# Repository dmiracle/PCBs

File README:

Created this file locally, then got it onto github. 133t

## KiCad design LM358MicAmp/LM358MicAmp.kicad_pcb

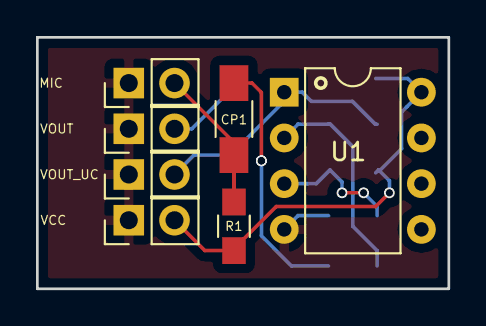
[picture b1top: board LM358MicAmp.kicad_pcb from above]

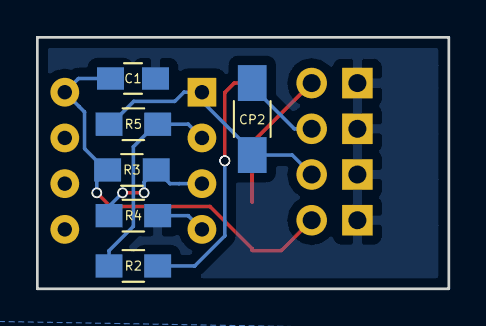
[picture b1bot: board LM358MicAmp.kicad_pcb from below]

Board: 2 copper layers, 22.9 x 14.0 mm, 13 parts (6 on the bottom side), 8 nets.

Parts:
C1: 100nF; C_0805_HandSoldering
CP1: 10uF; C_1206_HandSoldering
CP2: 220uF; C_1206_HandSoldering
MIC: CONN_01X02; Pin_Header_Straight_1x02_Pitch2.54mm
R1, R3, R4: 10K; R_0805_HandSoldering
R2: 1K; R_0805_HandSoldering
R5: 100K; R_0805_HandSoldering
U1: LM358; DIP-8_W7.62mm
VCC: CONN_01X02; Pin_Header_Straight_1x02_Pitch2.54mm
VOUT: CONN_01X02; Pin_Header_Straight_1x02_Pitch2.54mm
VOUT_UC: CONN_01X02; Pin_Header_Straight_1x02_Pitch2.54mm

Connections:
GND: C1.2, MIC.1, R4.2, U1.4, VCC.1, VOUT.1, VOUT_UC.1
MIC: CP1.1, MIC.2, R1.2
unnamed: CP1.2, R2.2
unnamed: R2.1, R5.2, U1.2
unnamed: R3.2, R4.1, U1.3
VCC: C1.1, R1.1, R3.1, U1.8, VCC.2
VOUT: CP2.2, VOUT.2
VOUT_UC: CP2.1, R5.1, U1.1, VOUT_UC.2

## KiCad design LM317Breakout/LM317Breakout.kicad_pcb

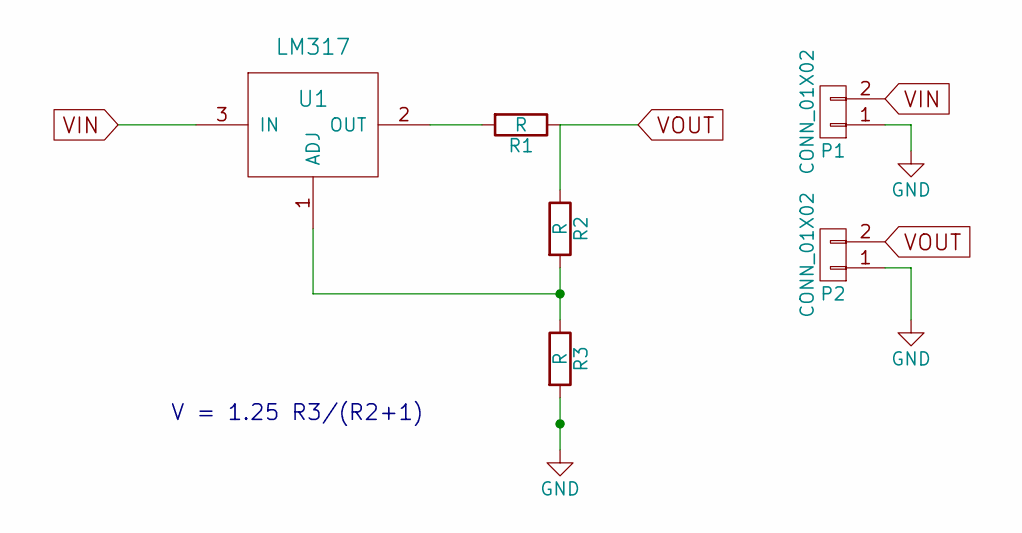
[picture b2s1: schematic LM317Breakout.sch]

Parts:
P1, P2: CONN_01X02; Pin_Header_Straight_1x02_Pitch2.54mm
R1, R2, R3: R; Socket_Strip_Straight_2x01_Pitch2.54mm
U1: LM317; Socket_Strip_Straight_1x03_Pitch2.54mm

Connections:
GND: P1.1, P2.1, R3.2
unnamed: R1.2, U1.2 (OUT)
unnamed: R2.2, R3.1, U1.1 (ADJ)
VIN: P1.2, U1.3 (IN)
VOUT: P2.2, R1.1, R2.1

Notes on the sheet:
V = 1.25 R3/(R2+1)

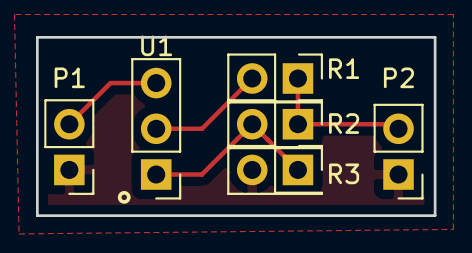
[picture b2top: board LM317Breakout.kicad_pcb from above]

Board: 2 copper layers, 22.1 x 9.9 mm, 6 parts (0 on the bottom side), 5 nets.

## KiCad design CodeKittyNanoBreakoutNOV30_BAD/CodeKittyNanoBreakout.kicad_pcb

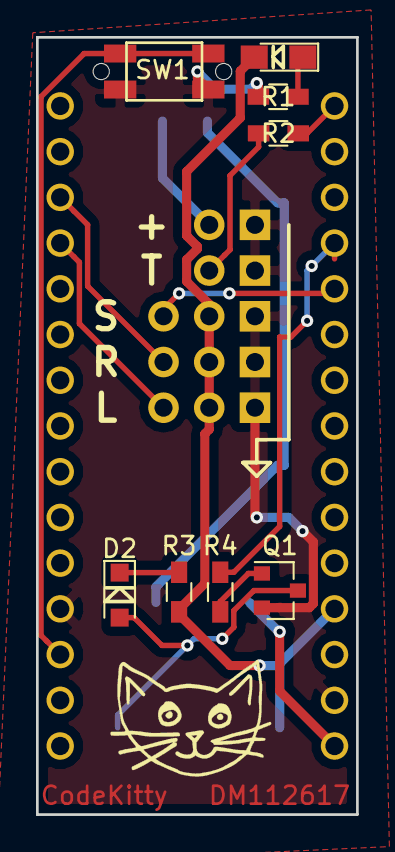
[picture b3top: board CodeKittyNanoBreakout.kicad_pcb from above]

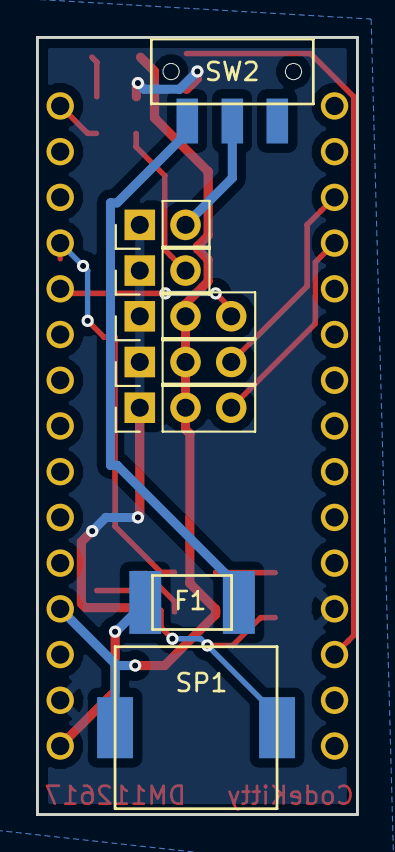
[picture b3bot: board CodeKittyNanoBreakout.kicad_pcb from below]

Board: 2 copper layers, 17.8 x 43.2 mm, 17 parts (9 on the bottom side), 16 nets.

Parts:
D1: LED; LED_0805_HandSoldering
D2: D; D_SOD-323_HandSoldering
F1: F_Small; DM_FUSE_PTC0ZCG
P1, P2: CONN_01X02; Pin_Header_Straight_1x02_Pitch2.54mm
P3, P4, P5: CONN_01X03; Pin_Header_Straight_1x03_Pitch2.54mm
Q1: MMBT3904; SOT-23
R1, R2, R3, R4: R; R_0603_HandSoldering
SP1: SPEAKER; DM_PiezSMD_PMKCS0909E4000-R1
SW1: SW_PUSH_SMALL_H; DM_SMD_BUTTON_PTS810
SW2: Switch_SPDT_x2; DM_SPDT_RTAngle_JS102011SAQN
U1: ArduinoNano

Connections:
5V: D1.2, P3.2, P4.2, P5.2, R3.1, SP1.1, U1.27
BUZZ: R4.2, U1.19
GND: P1.1, P2.1, P3.1, P4.1, P5.1, Q1.2, R1.2, SW1.2, U1.4, U1.29
LSERVO: P3.3, U1.12
unnamed: D1.1, R1.1
unnamed: D2.1, R3.2
unnamed: D2.2, Q1.3, SP1.2
unnamed: F1.1, SW2.3
unnamed: P1.2, SW2.2
unnamed: P2.2, R2.1
unnamed: Q1.1, R4.1
RSERVO: P4.3, U1.13
RST: SW1.1, U1.3
SENS: P5.3, U1.20
TAIL: R2.2, U1.16
VCC: F1.2, U1.30

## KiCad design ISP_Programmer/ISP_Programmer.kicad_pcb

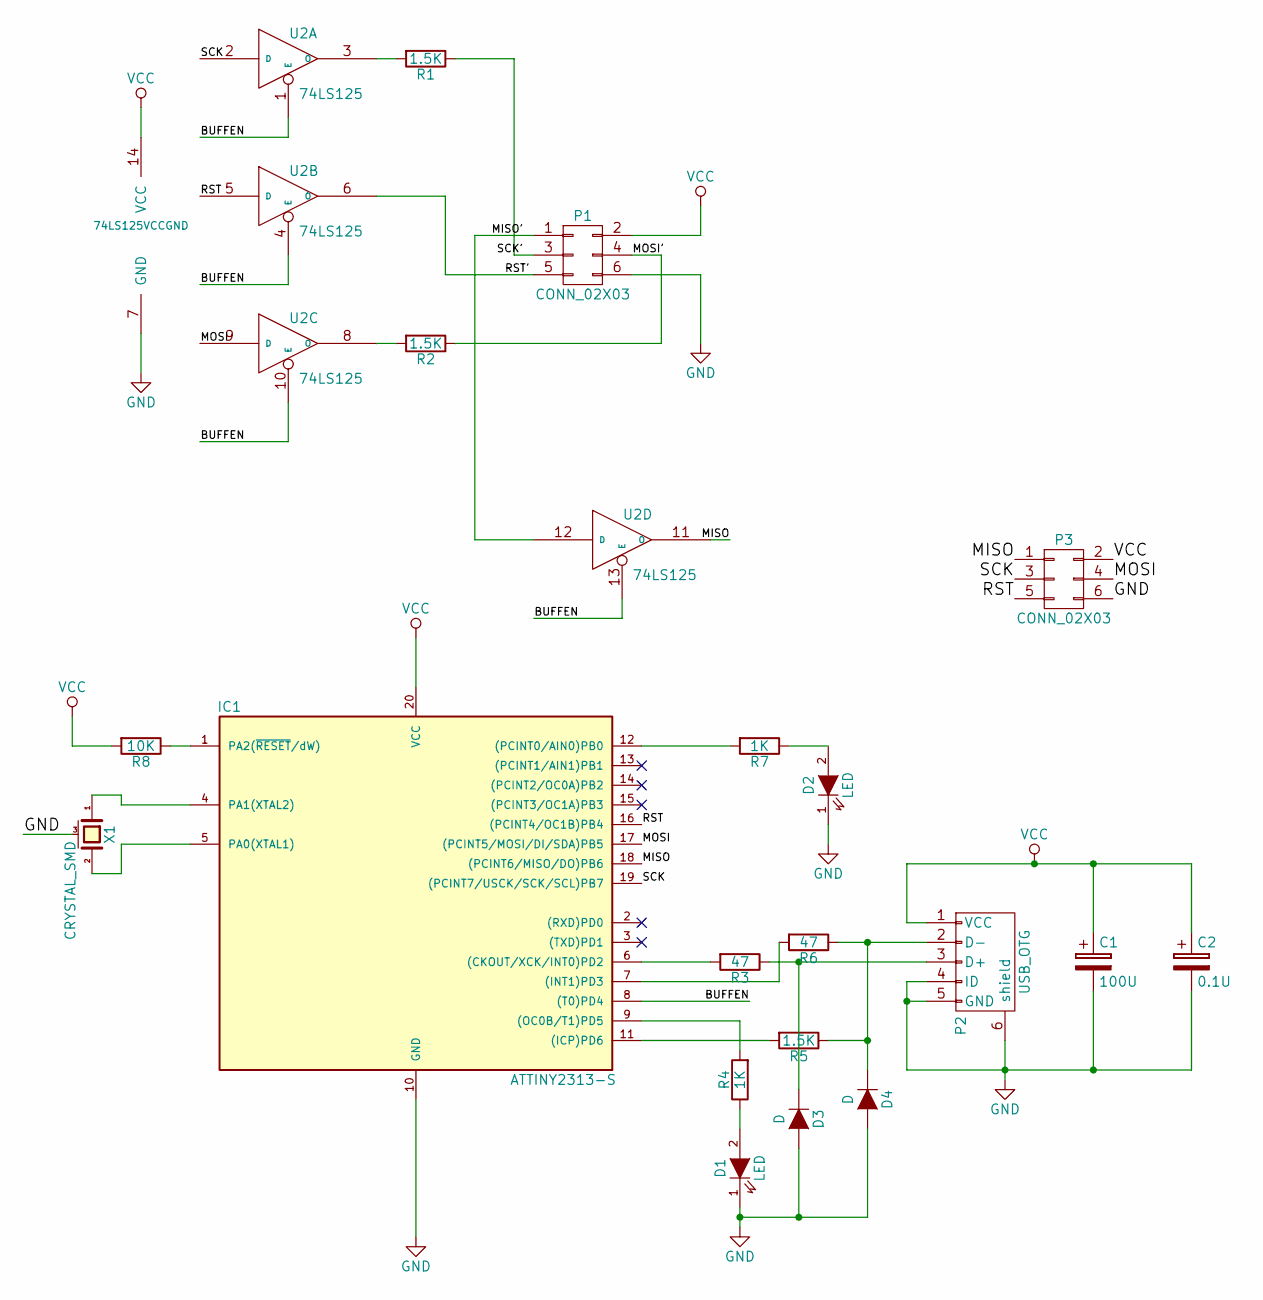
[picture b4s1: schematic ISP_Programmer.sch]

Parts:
C1: 100U; C_1206_HandSoldering
C2: 0.1U; C_0603_HandSoldering
D1, D2: LED; LED_0805
D3, D4: D; D_SOD-123
IC1: ATTINY2313-S; DM_ATTINY2313_20S2
P1, P3: CONN_02X03; Pin_Header_Straight_2x03_Pitch2.54mm
P2: USB_OTG; DM_USB_MICRO
R1, R2, R5: 1.5K; R_0603_HandSoldering
R3, R6: 47; R_0603_HandSoldering
R4, R7: 1K; R_0603_HandSoldering
R8: 10K; R_0603_HandSoldering
U2: 74LS125; DM_SOP14
X1: CRYSTAL_SMD; DM_PBRC-H

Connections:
/BUFFEN: IC1.8 ((T0)PD4), U2.1 (E), U2.4 (E), U2.10 (E), U2.13 (E)
/MISO: IC1.18 ((PCINT6/MISO/DO)PB6), P3.1, U2.11 (O)
/MISO': P1.1, U2.12 (D)
/MOSI: IC1.17 ((PCINT5/MOSI/DI/SDA)PB5), P3.4, U2.9 (D)
/MOSI': P1.4, R2.1
/RST: IC1.16 ((PCINT4/OC1B)PB4), P3.5, U2.5 (D)
/RST': P1.5, U2.6 (O)
/SCK: IC1.19 ((PCINT7/USCK/SCK/SCL)PB7), P3.3, U2.2 (D)
/SCK': P1.3, R1.1
unnamed: D1.2 (A), R4.1
unnamed: D2.2 (A), R7.1
unnamed: D3.1 (K), P2.3 (D+), R3.1
unnamed: D4.1 (K), P2.2 (D-), R5.1, R6.1
unnamed: IC1.1 (PA2(~RESET~/dW)), R8.1
unnamed: IC1.4 (PA1(XTAL2)), X1.1
unnamed: IC1.5 (PA0(XTAL1)), X1.2
unnamed: IC1.6 ((CKOUT/XCK/INT0)PD2), R3.2
unnamed: IC1.7 ((INT1)PD3), R6.2
unnamed: IC1.9 ((OC0B/T1)PD5), R4.2
unnamed: IC1.11 ((ICP)PD6), R5.2
unnamed: IC1.12 ((PCINT0/AIN0)PB0), R7.2
unnamed: R1.2, U2.3 (O)
unnamed: R2.2, U2.8 (O)

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
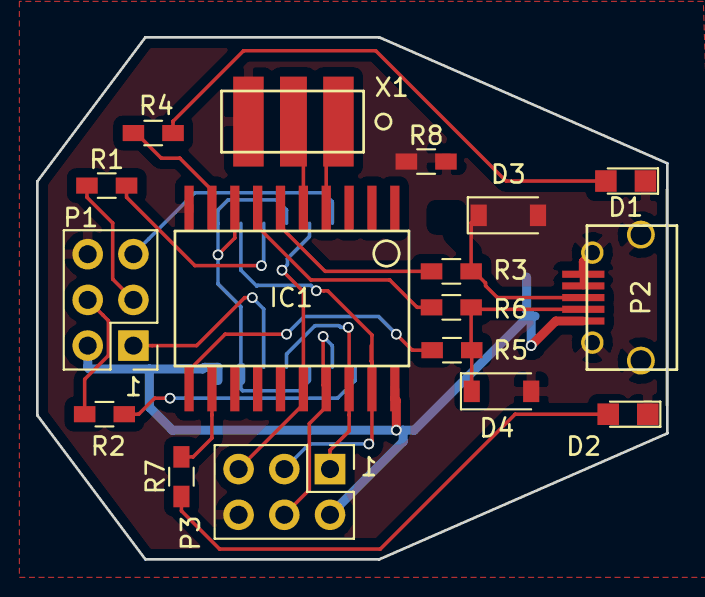
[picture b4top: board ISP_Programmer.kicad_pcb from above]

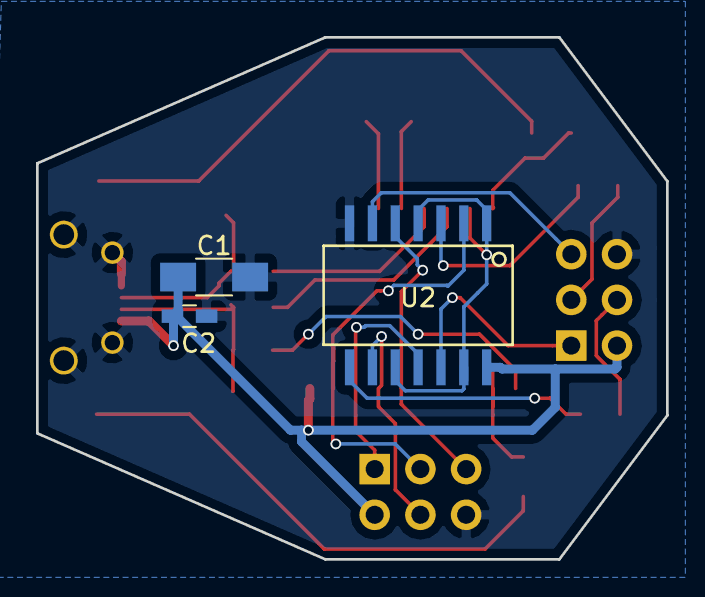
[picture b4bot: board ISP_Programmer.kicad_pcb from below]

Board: 2 copper layers, 35.0 x 29.0 mm, 20 parts (3 on the bottom side), 25 nets.

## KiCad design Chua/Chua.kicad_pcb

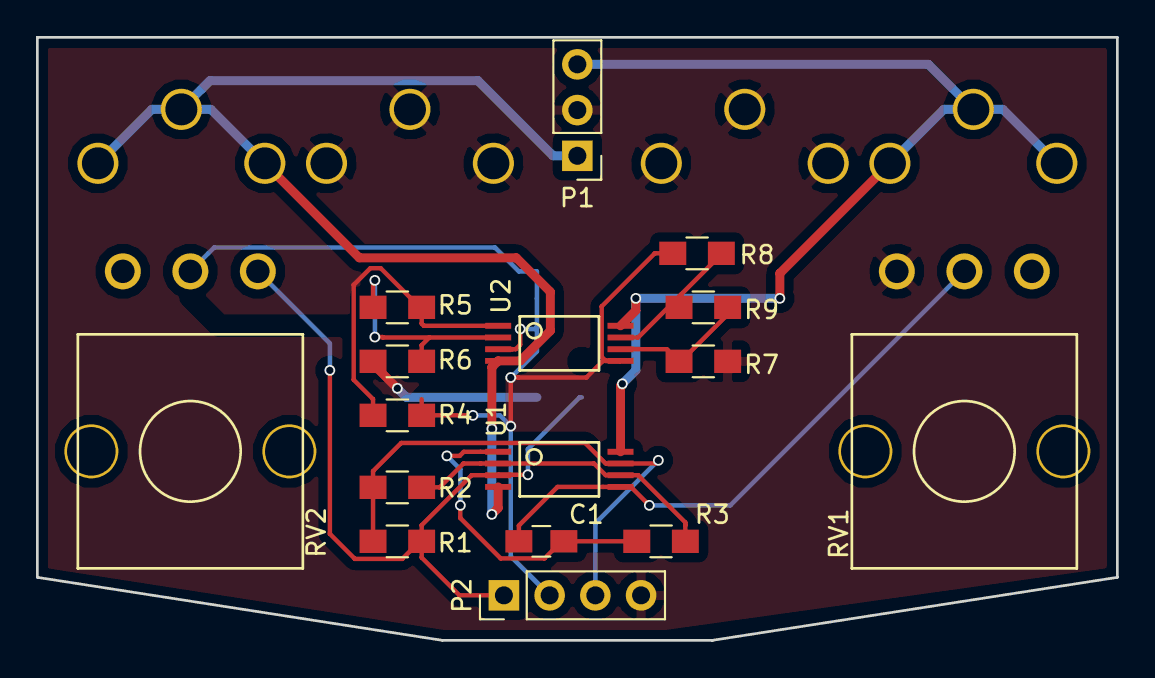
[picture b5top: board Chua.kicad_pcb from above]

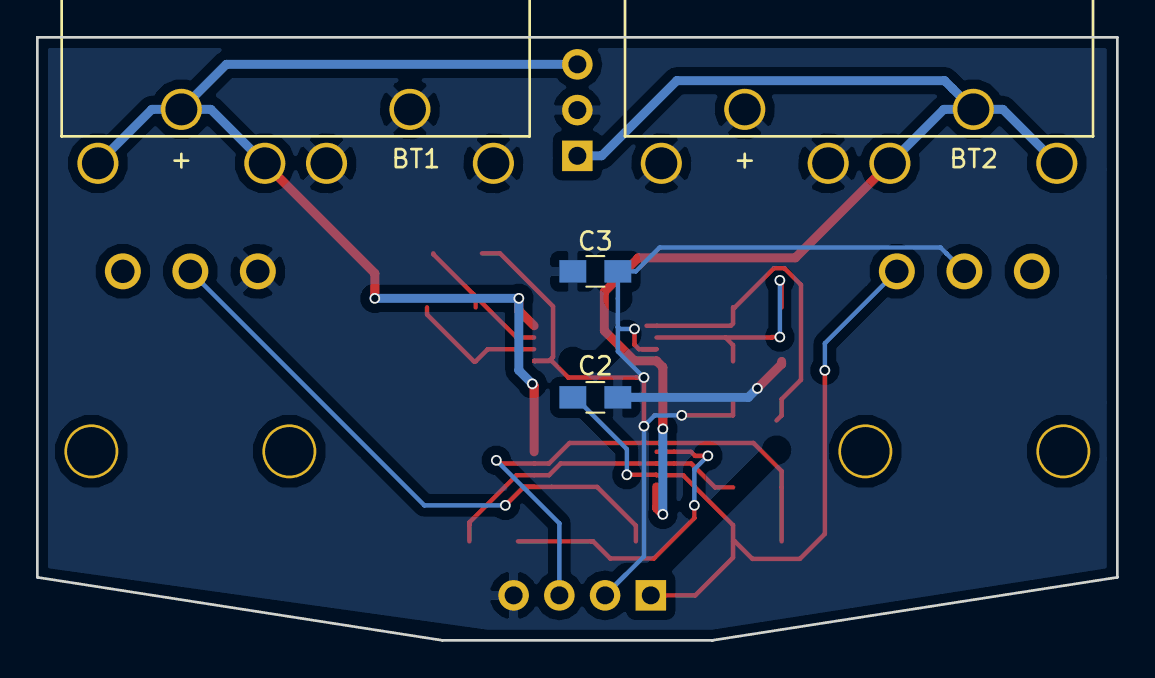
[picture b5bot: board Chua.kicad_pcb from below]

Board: 2 copper layers, 60.0 x 33.5 mm, 20 parts (4 on the bottom side), 13 nets.

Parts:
BT1, BT2: Battery_Cell; DM_9V_ON_BOARD
C1, C2, C3: C; C_0805_HandSoldering
P1: CONN_01X03; Pin_Header_Straight_1x03_Pitch2.54mm
P2: CONN_01X04; Pin_Header_Straight_1x04_Pitch2.54mm
R1, R2, R3, R4, R5, R6, R7, R8, R9: R; R_0805_HandSoldering
RV1, RV2: POT; DM_POT_296
U1, U2: TL082; DM_TSSOP8

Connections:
/P: P2.3, R1.2, R2.1, U1.7
/VCC+: BT1.1, P1.3, U1.8, U2.8
/VCC-: BT2.2, P1.1, U1.4, U2.4
/X: C2.1, P2.1, R1.1, RV2.1, U1.3
/Y: C3.1, P2.2, R4.1, R8.2, RV2.2, U2.3, U2.5
GND: BT1.2, BT2.1, C2.2, C3.2, P1.2, P2.4, R6.2, R7.2, RV1.3
unnamed: C1.1, R3.2, U1.1
unnamed: C1.2, RV1.2, U1.5
unnamed: R2.2, R3.1, U1.2, U1.6
unnamed: R4.2, R5.2, U2.1
unnamed: R5.1, R6.1, U2.2
unnamed: R7.1, R9.2, U2.6
unnamed: R8.1, R9.1, U2.7

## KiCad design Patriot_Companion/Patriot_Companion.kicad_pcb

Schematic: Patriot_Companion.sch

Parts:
C1, C2: 22p; ZF_SMD_NonPol_0603
C3, C4, C5, C9, C20, C24: 0u1; ZF_SMD_NonPol_0603
C6, C13, C14, C16: CP; ZF_SMD_pol_1206
C7, C10: C; ZF_SMD_NonPol_0603
C8, C12: 1u0; ZF_SMD_NonPol_0603
C15, C21, C25: 10u; ZF_SMD_pol_1206
D1: CD1206-S01575; ZF_SMD_pol_1206
D2, D6: D; ZF_SMD_pol_0805
D3: RXLED; ZF_SMD_pol_0805
D4: TXLED; ZF_SMD_pol_0805
D5: LED; ZF_SMD_pol_0805
F1, F2: Polyfuse; ZF_SMD_1812
L1: Ferrite_Bead; ZF_SMD_pol_0805
L2: MH2029-300Y; ZF_SMD_pol_0805
LED1, LED2, LED3: NeoPixel; SR_CUSTOM_NEO_PIX
P1: USB_OTG; ZF_CONN_USB-MICRO-B-SMD-holes
P2: POWER_IN; ZF_CONN_POWER_1x2
P3: CONN_01X07; ZF_CONN_1x7-hdr
P4: CONN_02X03; ZF_CONN_3x2_noshroud
P5: MOTOR_1; ZF_CONN_POWER_1x2
P6: MOTOR_2; ZF_CONN_POWER_1x2
P7: SERVO_HEADER; ZF_CONN_1x3_servo
R1, R2, R4, R8, R13, R14, R19: R; ZF_SMD_NonPol_0603
R3, R9, R10, R11, R12, R15, R16: 10k; ZF_SMD_NonPol_0603
R5: 1M; ZF_SMD_NonPol_0603
R6, R7: 1k; ZF_SMD_NonPol_0603
RV1, RV2: Varistor; ZF_SMD_NonPol_0603
SW1: SWITCH; ZF_SW_LS38
SW2, SW3: SWITCH; ZF_SW_Metal_Ball_Tactile
U1: SHT30-DIS-B; ZF_IC_DFN8-050
U2: ATMEGA32U4-A; ZF_IC_TQFP44-0-8
U4: LF33CDT-TRY; ZF_SMD_DPAK
U5, U7: BD6212HFP-TR; XV_Custom_BD621
U9: joystick; ZF_JOYSTICK
Y1: 16M; Crystal_SMD_3225-4pin_3.2x2.5mm

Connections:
+5V: C10.1, C14.1, C15.1, C16.1, C20.1, C21.1, C24.1, C25.1, D3.2, D4.2, D5.2, D6.1 (K), L2.1, LED1.4 (VCC), LED2.4 (VCC), LED3.4 (VCC), P4.2, P7.2, R1.1, R2.1, R4.2, SW2.2, SW3.2, U1.5 (VDD), U2.2 (UVCC), U2.14 (VCC), U2.34 (VCC), U4.3 (Vout), U5.1 (VREF), U5.7 (VCC), U7.1 (VREF), U7.7 (VCC), U9.1 (L/R+), U9.8 (U/D+)
BUTTON_A: R9.1, SW2.1, U2.26 ((T1/~OC4D~/ADC9)PD6)
BUTTON_B: R10.1, SW3.1, U2.25 ((ICP2/ADC8)PD4)
D+: R14.1, U2.4 (D+)
D-: R13.1, U2.3 (D-)
FIN1: R11.1, U2.30 ((ADC13/OC1B/OC4B/PCINT13)PB6), U5.3 (FIN)
FIN2: R15.1, U2.32 ((ICP3/CLK0/OC4A)PC7), U7.3 (FIN)
GND: C1.2, C2.2, C3.2, C4.2, C5.2, C6.2, C7.2, C8.2, C9.2, C10.2, C12.2, C13.2, C14.2, C15.2, C16.2, C20.2, C21.2, C24.2, C25.2, D2.2 (A), L1.1, LED1.2 (GND), LED2.2 (GND), LED3.2 (GND), P1.5, P2.1, P4.6, P7.3, R8.1, R9.2, R10.2, R11.2, R12.2, R15.2, R16.2, R19.2, RV1.2, RV2.2, SW1.1, U1.2 (ADDR), U1.7 (R), U1.8 (GND), U2.5 (UGND), U2.15 (GND), U2.23 (GND), U2.35 (GND), U2.43 (GND), U4.2 (GND), U5.4 (GND), U5.8 (TAB), U7.4 (GND), U7.8 (TAB), U9.4 (GND), U9.5 (GND), Y1.2, Y1.4
JOYSTICK_X: U2.37 ((ADC6/TDO)PF6), U9.7 (L/R)
JOYSTICK_Y: U2.36 ((ADC7/TDI)PF7), U9.6 (U/D)
MISO: P4.1, U2.11 ((PDO/MISO/PCINT3)PB3)
MOSI: P4.4, U2.10 ((PDI/MOSI/PCINT2)PB2)
NEOPIXEL: LED1.3 (DIN), U2.20 ((RXD/INT2)PD2)
unnamed: C1.1, R5.1, U2.17 (XTAL1), Y1.1
unnamed: C2.1, R5.2, U2.16 (XTAL2), Y1.3
unnamed: C4.1, C5.1, D1.1 (K), R3.1
unnamed: C8.1, U2.6 (UCAP)
unnamed: C9.1, R4.1, U2.42 (AREF)
unnamed: C12.1, L2.2, U2.24 (AVCC), U2.44 (AVCC)
unnamed: C3.1, C13.1, D2.1 (K), F2.1, U4.1 (Vin)
unnamed: D3.1, R6.1
unnamed: D4.1, R7.1
unnamed: D5.1, R19.1
unnamed: F1.2, P1.1
unnamed: F2.2, P2.2
unnamed: L1.2, P1.6
unnamed: LED1.1 (DOUT), LED2.3 (DIN)
unnamed: LED2.1 (DOUT), LED3.3 (DIN)
unnamed: P1.2, R13.2, RV1.1
unnamed: P1.3, R14.2, RV2.1
unnamed: P3.1, U2.1 ((INT6/AIN0)PE6)
unnamed: P3.2, U2.41 ((ADC0)PF0)
unnamed: P3.3, U2.40 ((ADC1)PF1)
unnamed: P3.4, U2.39 ((ADC4/TCK)PF4)
unnamed: P3.5, U2.38 ((ADC5/TMS)PF5)
unnamed: P5.1, U5.2 (OUT1)
unnamed: P5.2, U5.6 (OUT2)
unnamed: P6.1, U7.2 (OUT1)
unnamed: P6.2, U7.6 (OUT2)
unnamed: R6.2, U2.8 ((SS/PCINT0)PB0)
unnamed: R7.2, U2.22 ((XCK1/~CTS~)PD5)
unnamed: R8.2, U2.33 ((~HWB~)PE2)
RESET: D1.2 (A), P4.5, R3.2, SW1.2, U2.13 (~RESET~)
RIN1: R12.1, U2.29 ((ADC12/OC1A/~OC4B~/PCINT12)PB5), U5.5 (RIN)
RIN2: R16.1, U2.31 ((OC3A/~OC4A~)PC6), U7.5 (RIN)
SCK: P4.3, U2.9 ((SCLK/PCINT1)PB1)
SCL: P3.6, R1.2, U1.4 (SCL), U2.18 ((OC0B/SCL/INT0)PD0)
SDA: P3.7, R2.2, U1.1 (SDA), U2.19 ((SDA/INT1)PD1)
SERVO: P7.1, U2.27 ((T0/OC4D/ADC10)PD7)
VUSB: C6.1, C7.1, D6.2 (A), F1.1, U2.7 (VBUS)

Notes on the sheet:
NEOPIXELS (EIGHT)
DC MOTOR 1
DC MOTOR 2
SERVO
ANALOG JOYSTICK
BUTTONS
AVR ISP HEADER
RESET BUTTON
REGULATOR
PROCESSOR CORE
USB TX/RX LEDS
USB DATA/POWER

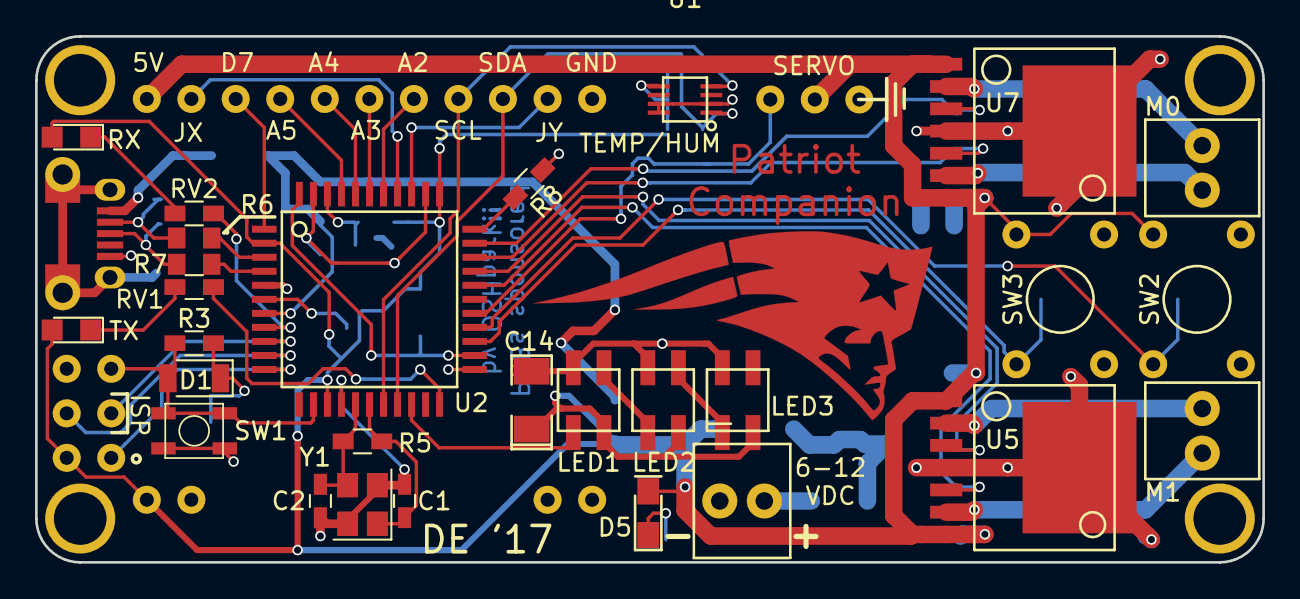
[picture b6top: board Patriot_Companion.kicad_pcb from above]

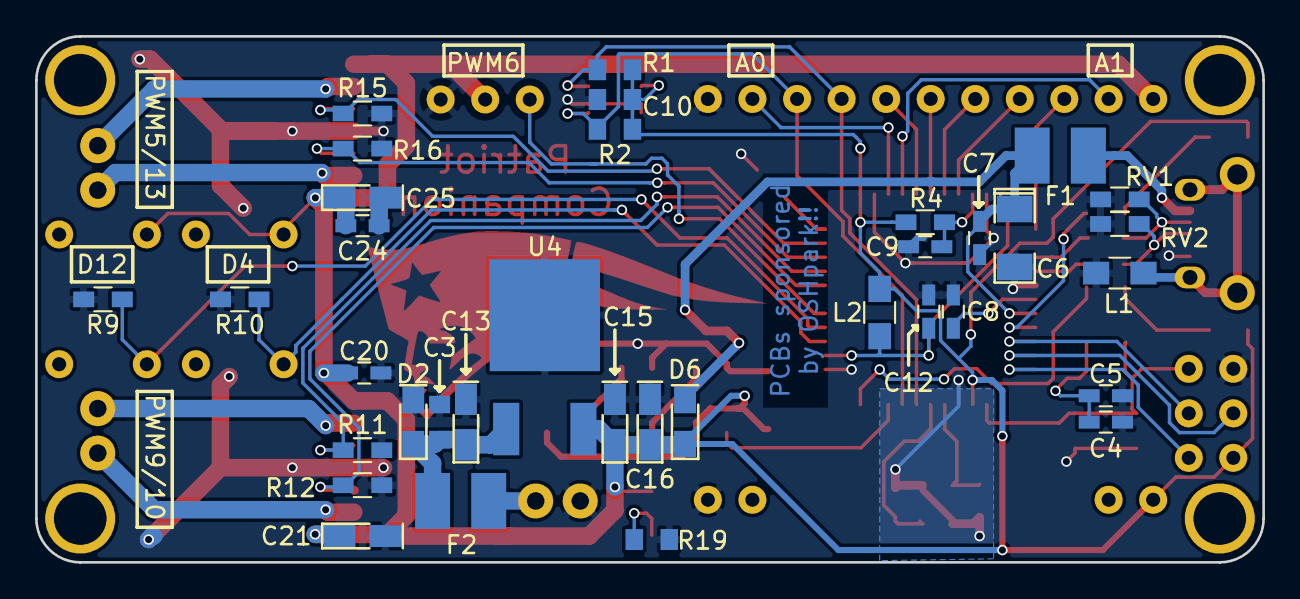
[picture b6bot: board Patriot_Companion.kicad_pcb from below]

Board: 2 copper layers, 70.0 x 30.0 mm, 68 parts (35 on the bottom side), 50 nets.

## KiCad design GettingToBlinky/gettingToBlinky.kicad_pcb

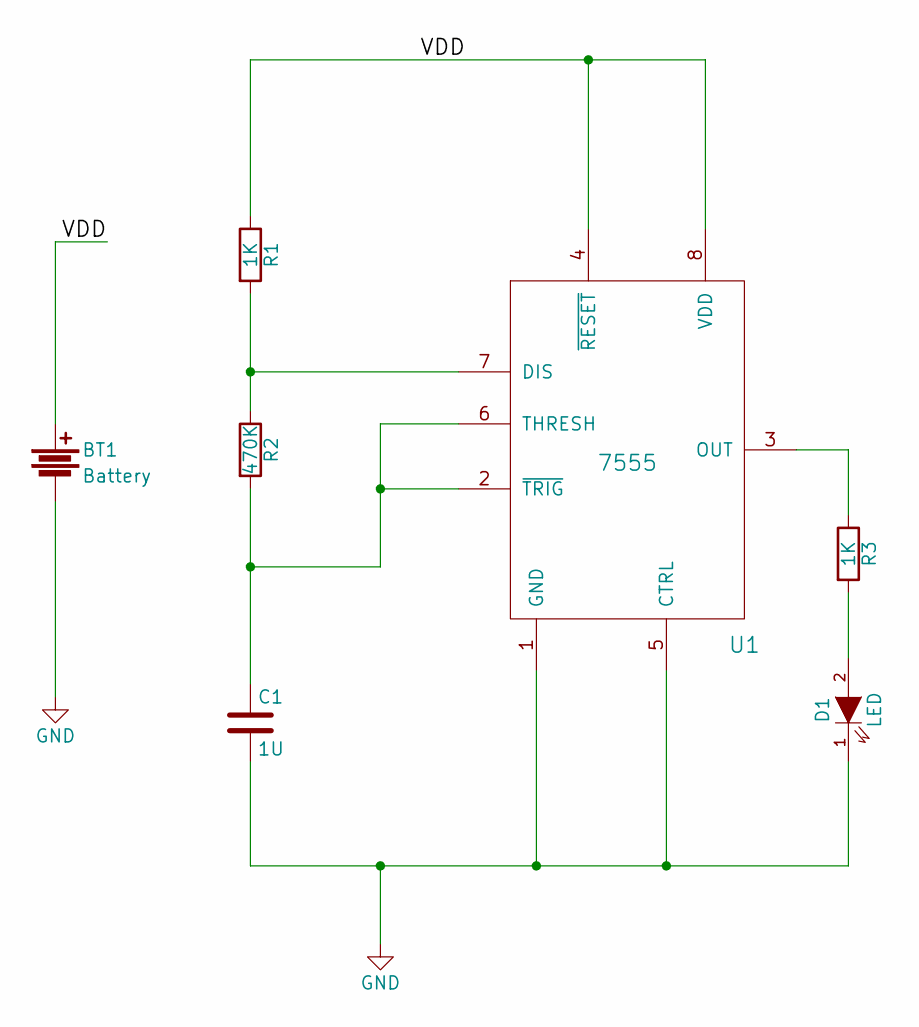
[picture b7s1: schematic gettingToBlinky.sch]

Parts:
BT1: Battery; S8211R
C1: 1U; C_1206_HandSoldering
D1: LED; LED_0805
R1, R3: 1K; R_0805_HandSoldering
R2: 470K; R_0805_HandSoldering
U1: 7555; SOIC-8_3.9x4.9mm_Pitch1.27mm

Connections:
/VDD: BT1.1, R1.1, U1.4 (~RESET), U1.8 (VDD)
GND: BT1.2, C1.2, D1.1 (K), U1.1 (GND), U1.5 (CTRL)
unnamed: C1.1, R2.2, U1.2 (~TRIG), U1.6 (THRESH)
unnamed: D1.2 (A), R3.2
unnamed: R1.2, R2.1, U1.7 (DIS)
unnamed: R3.1, U1.3 (OUT)

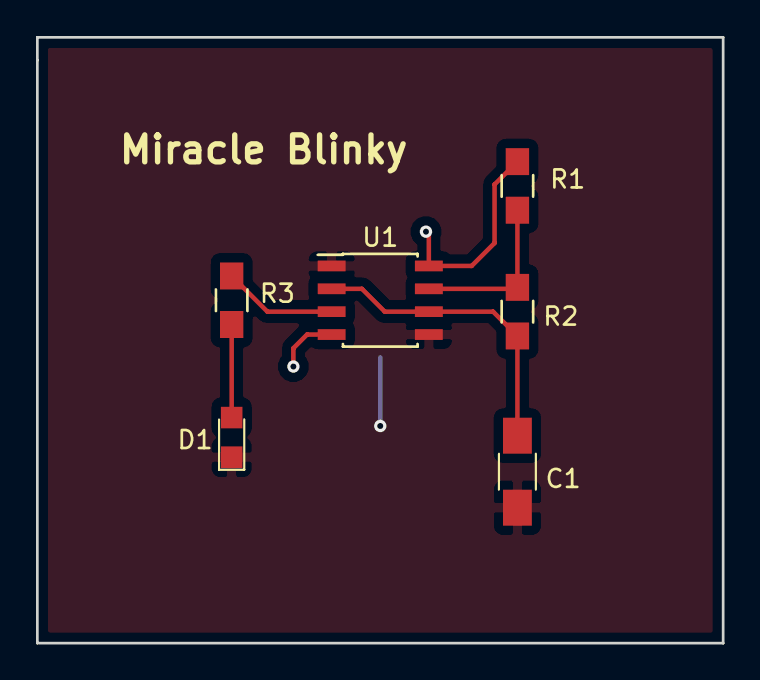
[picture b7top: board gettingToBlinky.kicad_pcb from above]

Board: 2 copper layers, 38.1 x 33.7 mm, 7 parts (1 on the bottom side), 6 nets.

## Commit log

2017-02-05 FIRST
2017-02-05 Added README
2017-02-05 assigned R and C footprint
2017-02-26 Adding sousvide project
2017-03-10 Added relay symbol
2017-03-13 Added SPI/ISP proogramming header
2017-05-09 Added patriot companion
2017-05-09 started PC routes
2017-05-09 introduce Simplified Patrio Companion
2017-05-09 Added a logo
2017-05-10 something
2017-05-23 started ISP programmer
2017-05-24 ISP footprints
2017-05-25 ISP done
2017-05-25 ISP pcb small touch ups
2017-05-26 checking
2017-05-31 chua pcb traces
2017-05-31 chua redesigned board for smallerness
2017-05-31 added label to chua
2017-06-01 adding output to chua
2017-06-05 fixed incorrect chua diode connection
2017-06-06 added ISP programmer reset pull up
2017-10-08 added things
2017-10-10 update of codekitty
2017-10-10 added fsilk letters for connectors for codeKitty
2017-10-10 moved led to fside ck
2017-10-15 updated CK board
2017-11-07 kitty3
2017-11-15 some cknano
2017-11-20 getting to 1.0
2017-11-24 Chua resistor values
2017-11-24 Clean up
2017-11-28 ServoTester first commit
2017-12-06 Patriot companion schematic updated for printing
2017-12-06 added archive of PCB with bad traces
2017-12-11 fixed CKN
2017-12-11 started reverse engineering a cheap servo
2017-12-20 added LM358 simple amp
2017-12-24 CK Nano BAD for ref
2018-01-22 LM358 and LM317 bobs
